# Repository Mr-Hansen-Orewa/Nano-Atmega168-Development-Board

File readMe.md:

# Read Me

## Overview
I am designing a development board for year 11 students (15-16 year olds) to use in 2023

## Parts list
- Arduino Nano with Atmega168 controller 
- Yellow LED
- RGB LED
- Trimpot
- LDR
- 3 switch DIP switch
- Button

## Pinout and Headers
 - D0 - goes to a header.
 - D1 - goes to a header.
 - D2 - momentary switch.
 - D3 - goes to a header.
 - D4 - DIP switch 1.
 - D5 - goes to a header.
 - D6 - goes to a header.
 - D7 - DIP switch 2.
 - D8 - DIP switch 3.
 - D9 - RGB LED Blue/Green (silkscreen issues).
 - D10 - RGB LED Blue/Green (silkscreen issues).
 - D11 - RGB LED Red.
 - D12 - goes to a header.
 - D13 - Yellow LED.
 - D14/A0 - LDR.
 - D15/A1 - trimpot.
 - D16/A2 - goes to a header.
 - D17/A3 - goes to a header.
 - D18/A4 - goes to a header.
 - D19/A5 - goes to a header.
 - A6 - goes to a header.
 - A7 - goes to a header.

## Cool bits
I used the import bmp script in the automate menu to put the logo on the silkscreen. 

I also put a testpoint rectangle in the tStop layer to leave it as exposed copper for a GND testpoint.

## Future ideas/versions
Have a qwiic / stemmaQT connector on the I2C pins its a JST SH 4-pin Vertical Connector on Adafruit.
Or have an led matrix board directly soldered to the I2C pins.
Or another button without the debounce resistor - maybe both buttons have resistors but also those PCB jumper solder pads to enable or disable them once shown button bounce issues.
https://youtu.be/uOp_2-7_1Hw.

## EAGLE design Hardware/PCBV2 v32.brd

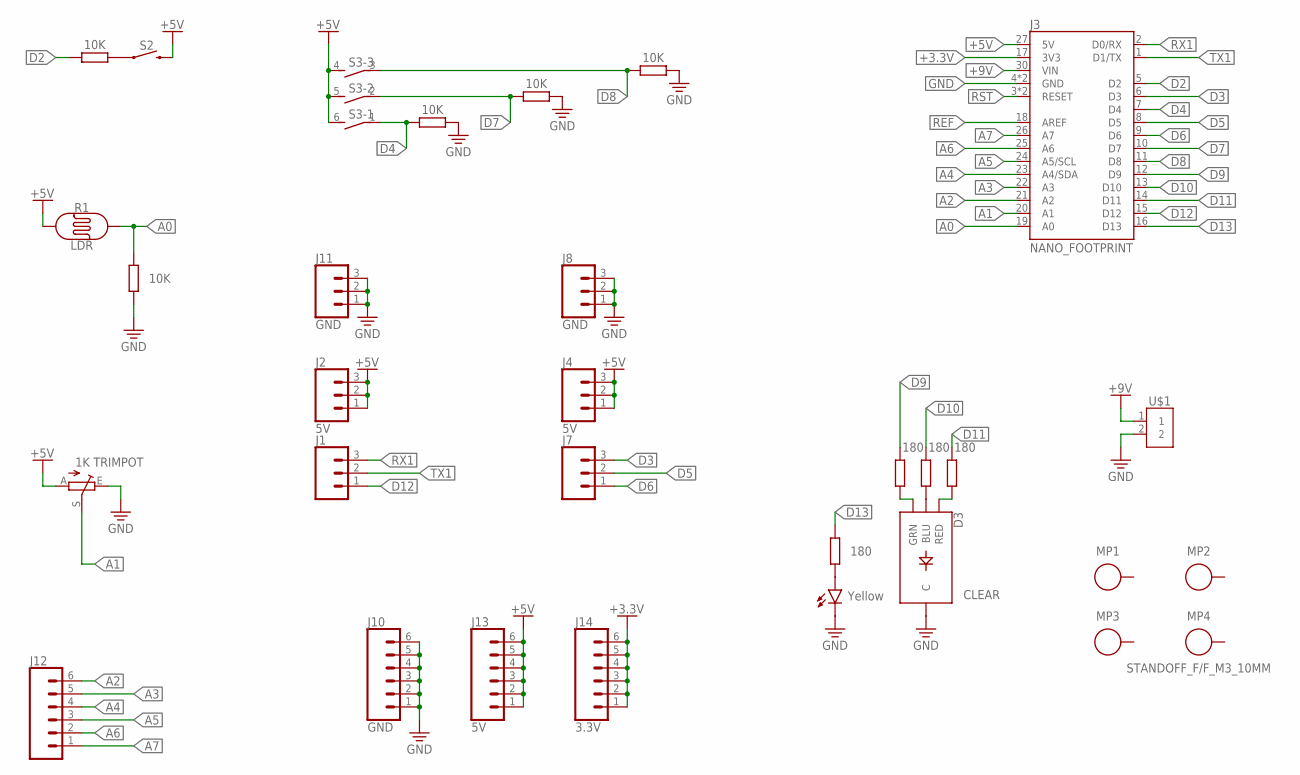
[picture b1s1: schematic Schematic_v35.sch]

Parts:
D2: Yellow; LED_5MM
D3: CLEAR; LED-RGB-THRU
J1, J7: CONN_03; 1X03
J2, J4: 5V; 1X03
J3: NANO_FOOTPRINT; NANO
J8, J11: GND; 1X03
J10: GND; 1X06
J12: CONN_06SILK_FEMALE_PTH; 1X06
J13: 5V; 1X06
J14: 3.3V; 1X06
MP1, MP2, MP3, MP4: STANDOFF_F/F_M3_10MM; STANDOFF_HEX_FEMALE_550X1000_M3X0.5_MTGP850H320
R1: LDR; PHOTOCELL-KIT
R3, R6, R7, R8: 180; RESAD724W46L381D178B
R4: 1K TRIMPOT; B25P
R5, R9, R10, R11, R12: 10K; RESAD724W46L381D178B
S2: BUTTON; TACTILE_SWITCH_PTH_6.0MM_KIT
S3: DIP SWITCH; DS-03
U$1: 2828XX-2282837-2; TERMBLK_508-2N

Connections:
+3.3V: J3.17 (3V3), J14.1, J14.2, J14.3, J14.4, J14.5, J14.6
+5V: J2.1, J2.2, J2.3, J3.27 (5V), J4.1, J4.2, J4.3, J13.1, J13.2, J13.3, J13.4, J13.5, J13.6, R1.1, R4.A, S2.3 (2), S3.4 (2), S3.5 (2), S3.6 (2)
+9V: J3.30 (VIN), U$1.1
A0: J3.19 (A0), R1.2, R9.2
A1: J3.20 (A1), R4.S
A2: J3.21 (A2), J12.6
A3: J3.22 (A3), J12.5
A4: J3.23 (A4/SDA), J12.4
A5: J3.24 (A5/SCL), J12.3
A6: J3.25 (A6), J12.2
A7: J3.26 (A7), J12.1
D2: J3.5 (D2), R5.2
D3: J3.6 (D3), J7.3
D4: J3.7 (D4), R12.2, S3.1
D5: J3.8 (D5), J7.2
D6: J3.9 (D6), J7.1
D7: J3.10 (D7), R11.2, S3.2 (1)
D8: J3.11 (D8), R10.2, S3.3 (1)
D9: J3.12 (D9), R6.2
D10: J3.13 (D10), R7.2
D11: J3.14 (D11), R8.2
D12: J1.1, J3.15 (D12)
D13: J3.16 (D13), R3.2
GND: D2.K (C), D3.2 (C), J3.4 (GND), J3.29 (GND), J8.1, J8.2, J8.3, J10.1, J10.2, J10.3, J10.4, J10.5, J10.6, J11.1, J11.2, J11.3, R4.E, R9.1, R10.1, R11.1, R12.1, U$1.2
unnamed: D2.A, R3.1
unnamed: D3.3 (GRN), R6.1
unnamed: R5.1, S2.1
unnamed: D3.4 (BLU), R7.1
unnamed: D3.1 (RED), R8.1
REF: J3.18 (AREF)
RST: J3.3 (RESET), J3.28 (RESET)
RX1: J1.3, J3.2 (D0/RX)
TX1: J1.2, J3.1 (D1/TX)

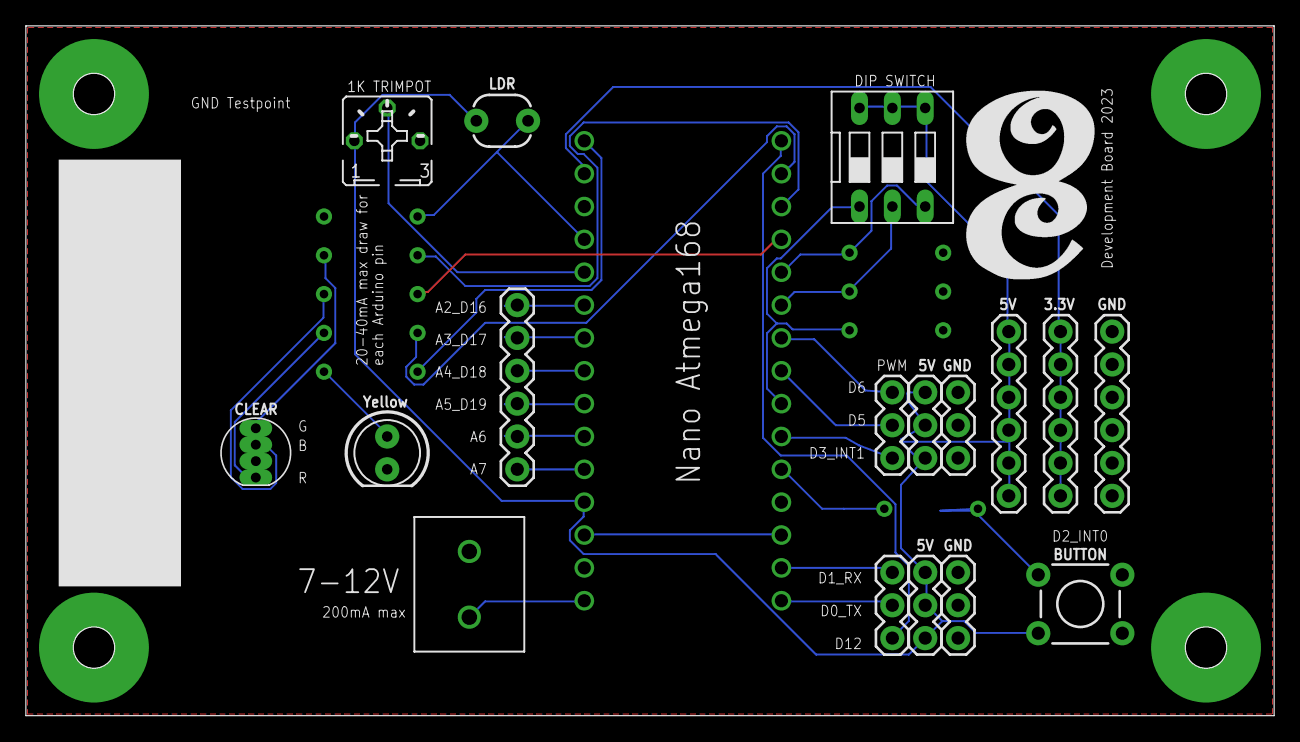
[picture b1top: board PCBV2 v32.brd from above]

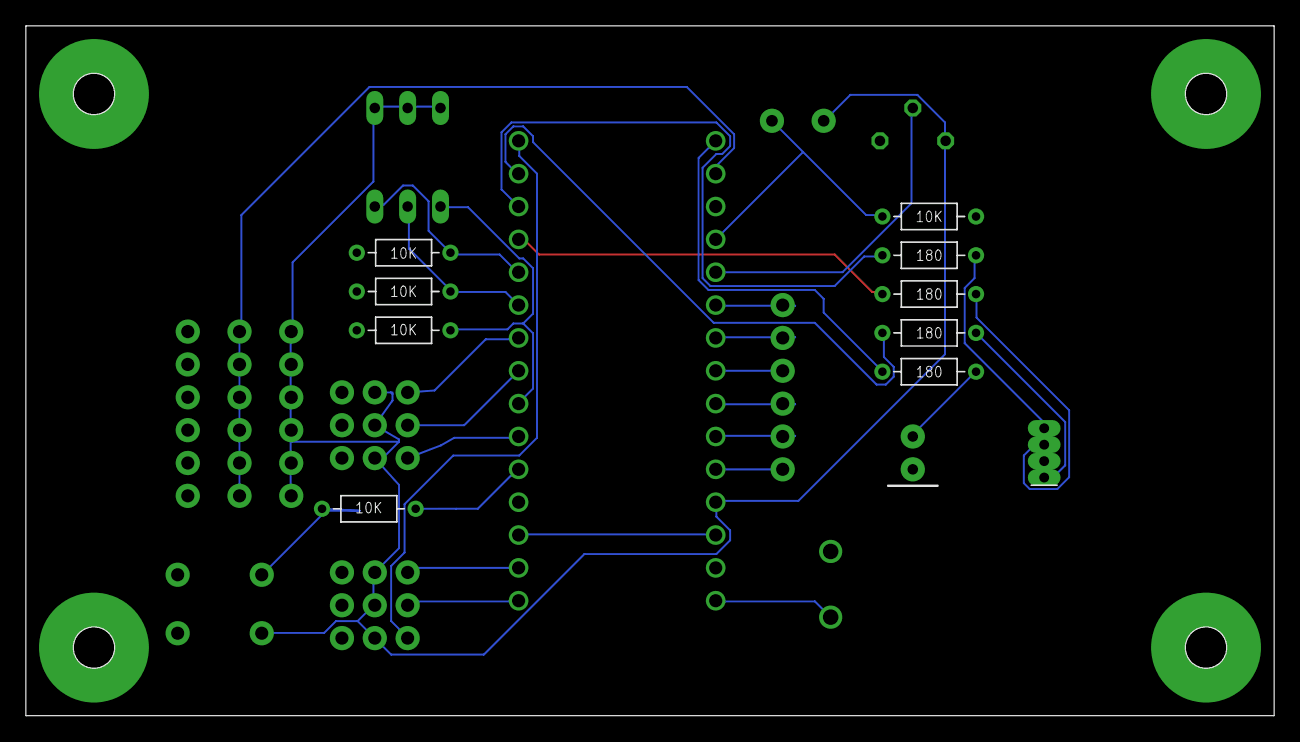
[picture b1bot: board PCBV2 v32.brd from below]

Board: 2 copper layers, 96.5 x 53.3 mm, 31 parts (13 on the bottom side), 32 nets.

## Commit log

2022-08-13 Add files via upload
    Black and white bmp of the college logo
    Follow the below steps to import BMP file in Fusion 360 PCB workspace:
    Open the Fusion 360 PCB workspace.
    Go to the 2D layout file and select the Automation tab.
    Choose Run ULP option, browse and select from the list the ULP file called "import-bmp" in Fusion 360.
    Select the .bmp file from a computer location to import the file to Fusion 360.
2022-08-13 Create readMe
    Quick overview and trying the basic formatting syntax
2022-08-13 Create Electronics Design v34.f3z
    added export of schematic and PCB
2022-08-14 adding files
2022-08-15 added board files
2022-08-25 changes to pcb
    updated the rgb led as pads touching
    also the silkscreen to label pins and give thicker traces
2022-08-27 code update
    added testing software v1
    also future ideas section to readMe
2022-08-28 minor updates
2023-02-26 examples added
    added basic and extension code examples that students would try and type up to test board and their programming skills
2023-03-10 Create random.ino
    added random code
2023-03-12 added code examples
    fixed DIP added some RGB code too
    RGB4 is intended as a excellence exemplar but needs more modification and testing
2024-01-30 Create buzzer.ino
    added a buzzer in 2024
    tone works better than digitalWrite

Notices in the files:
parts and their libraries:
SparkFun-LED: Licensing: Creative Commons ShareAlike 4.0 International - https://creativecommons.org/licenses/by-sa/4.0
